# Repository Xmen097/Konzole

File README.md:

# Konzole
Herní konzole s Atmega328 vytvořená v rámci kroužku v DDM Praha 6.

##### Hardware
- TFT display 320x240
- Custom joystick
- 8 tlačítek
- IR vysílač a přijímač
- Otočný potenciometr
- Nabíjecí li-ion baterie s nabíjecím obvodem na micro USB

##### Software
Implementovány byly hry:
 Pong, Tetris, Snake (credits: Vojtěch Černý), pacman, Space shooter

##### Obrázky

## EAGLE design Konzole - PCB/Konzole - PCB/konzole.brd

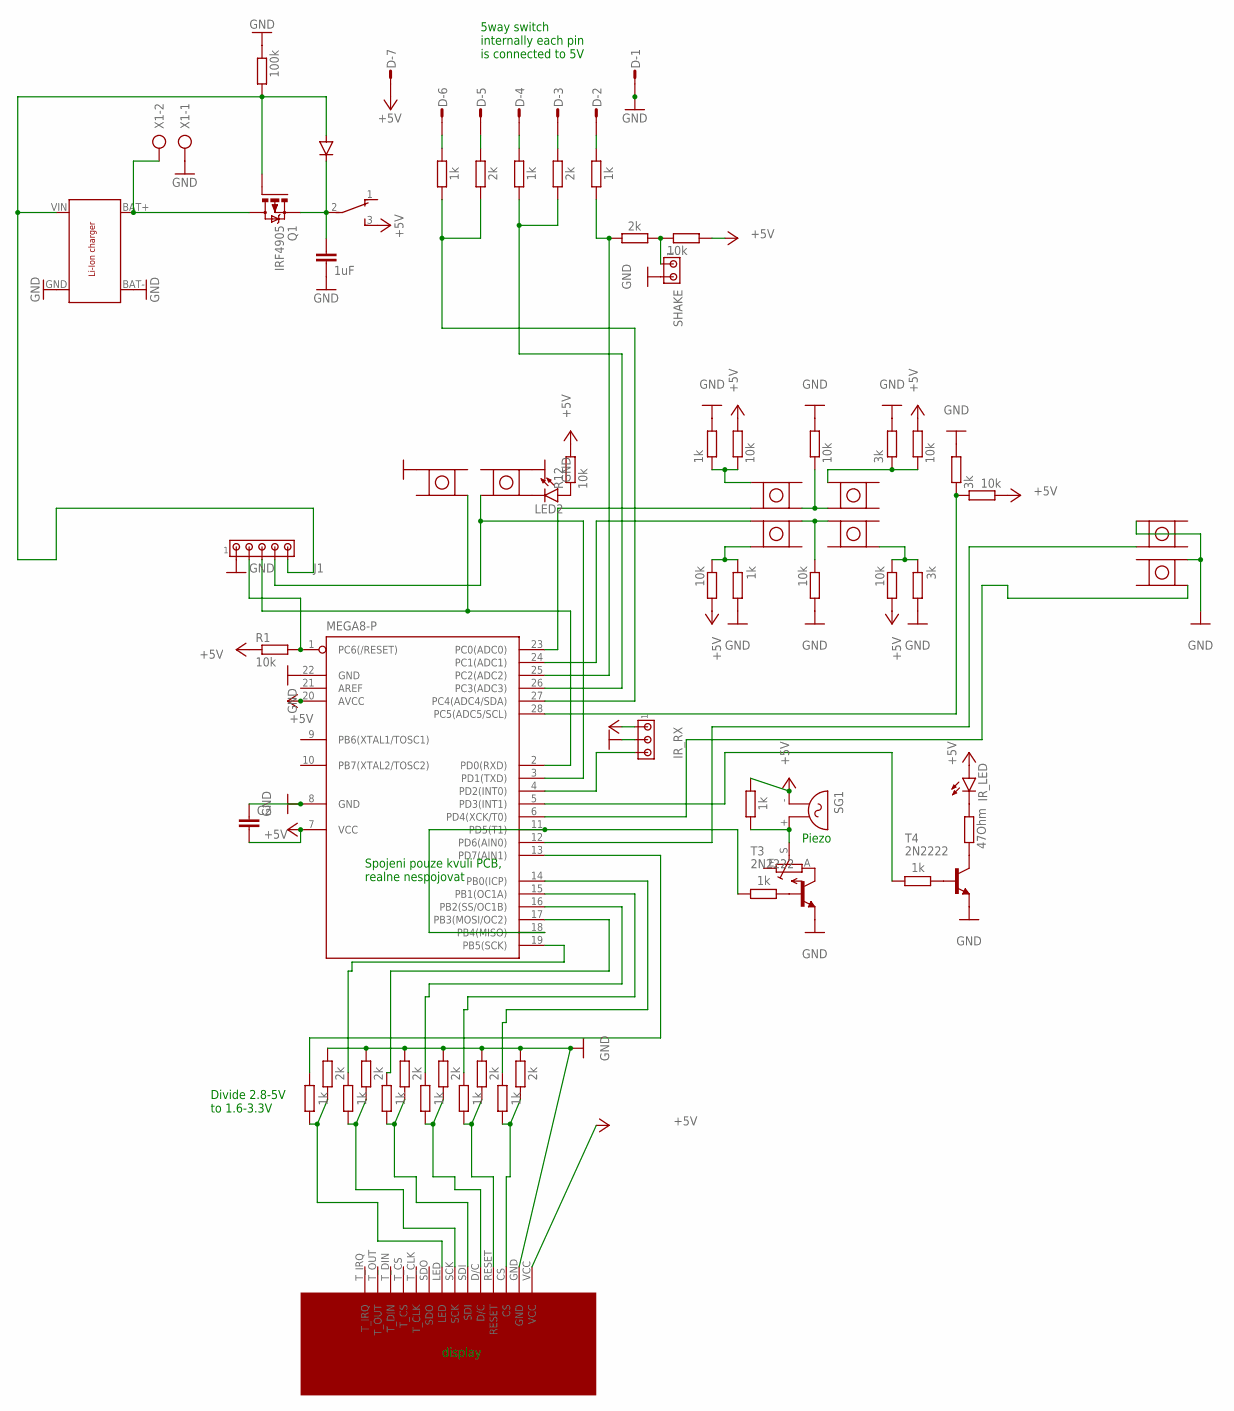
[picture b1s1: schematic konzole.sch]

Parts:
C1: 1uF; C050-025X075
C2: C5/2.5; C5B2.5
D: L07P
D1: 1N4004; DO41-10
IC1: MEGA8-P; DIL28-3
IR_LED: LED5MM
IR_RX: MTA03-100; 10X03MTA
J1: MTA05-100; 10X05MTA
LED2: LED3MM
Q1: IRF4905; TO220BH
R1, R12, R14, R16, R18, R20, R22, R23, R29, R49: 10k; 0207/10
R2, R4, R6, R8, R10, R15, R19, R24, R26, R27, R33, R35, R38, R40: 1k; 0207/10
R3, R5, R7, R9, R11, R25, R36, R39, R41: 2k; 0207/10
R13, R17, R21: 3k; 0207/10
R28: TRIM_EU-CIP20C-6MM; CIP20C-6MM
R34: 47Ohm; 0207/10
R42: 100k; 0207/10
S1: TL36PO; TL3XPO
SG1: F/QMX
SHAKE: MTA02-100; 10X02MTA
T3, T4: 2N2222; TO92-EBC-OVAL
U$1, U$3, U$4, U$5, U$6, U$7, U$8, U$9: TACT
U$2: DISPLAY
U$10: LI_ION_CHARGER
X1: AK500/2

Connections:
+5V: C2.2, D.7, IC1.7 (VCC), IC1.20 (AVCC), IR_LED.A, IR_RX.1, R1.1, R12.2, R14.2, R16.2, R18.2, R20.2, R27.2, R29.1, R49.2, S1.3 (S), SG1.- (1), U$2.VCC
GND: C1.2, C2.1, D.1, IC1.8 (GND), IC1.22 (GND), IR_RX.2, J1.1, R3.2, R5.2, R7.2, R9.2, R11.2, R13.2, R15.2, R17.2, R19.2, R21.2, R22.2, R23.2, R25.2, R42.2, SHAKE.2, T3.E, T4.E, U$2.GND, U$6.P$4 (4), U$7.P$1 (1), U$8.P$1 (1), U$9.P$4 (4), U$10.BAT-, U$10.GND, X1.1
unnamed: IC1.1 (PC6(/RESET)), J1.2, R1.2
unnamed: R2.2, R3.1, U$2.CS
unnamed: R4.2, R5.1, U$2.RESET
unnamed: R6.2, R7.1, U$2.D/C
unnamed: R8.2, R9.1, U$2.SDI
unnamed: R10.2, R11.1, U$2.SCK
unnamed: IC1.17 (PB3(MOSI/OC2)), R8.1
unnamed: IC1.13 (PD7(AIN1)), R24.1
unnamed: IC1.16 (PB2(SS/OC1B)), R6.1
unnamed: IC1.15 (PB1(OC1A)), R4.1
unnamed: R14.1, R15.1, U$1.P$1 (1)
unnamed: R27.1, R28.S, SG1.+ (2)
unnamed: IC1.19 (PB5(SCK)), R10.1
unnamed: R16.1, R17.1, U$5.P$1 (1)
unnamed: R18.1, R19.1, U$3.P$2 (2)
unnamed: R20.1, R21.1, U$4.P$3 (3)
unnamed: R33.2, T4.B
unnamed: LED2.K (C), U$9.P$3 (3)
unnamed: IC1.2 (PD0(RXD)), J1.3, U$8.P$3 (3)
unnamed: IC1.3 (PD1(TXD)), J1.4, U$9.P$2 (2)
unnamed: R23.1, U$3.P$4 (4), U$4.P$1 (1)
unnamed: R22.1, U$1.P$3 (3), U$5.P$2 (2)
unnamed: IC1.23 (PC0(ADC0)), U$1.P$2 (2)
unnamed: R24.2, R25.1, U$2.LED
unnamed: IC1.24 (PC1(ADC1)), U$3.P$1 (1)
unnamed: R34.1, T4.C
unnamed: IC1.11 (PD5(T1)), IC1.18 (PB4(MISO)), R26.1
unnamed: R26.2, T3.B
unnamed: R28.A, T3.C
unnamed: IC1.14 (PB0(ICP)), R2.1
unnamed: IC1.12 (PD6(AIN0)), U$7.P$2 (2)
unnamed: IC1.28 (PC5(ADC5/SCL)), R13.1, R29.2
unnamed: IC1.6 (PD4(XCK/T0)), U$6.P$3 (3)
unnamed: LED2.A, R12.1
unnamed: IC1.4 (PD2(INT0)), IR_RX.3
unnamed: IR_LED.K (C), R34.2
unnamed: IC1.5 (PD3(INT1)), R33.1
unnamed: D.6, R38.2
unnamed: D.5, R36.2
unnamed: D.4, R35.2
unnamed: Q1.D, U$10.BAT+, X1.2
unnamed: D.3, R39.2
unnamed: D.2, R40.2
unnamed: IC1.26 (PC3(ADC3)), R35.1, R39.1
unnamed: R41.1, R49.1, SHAKE.1
unnamed: D1.A, J1.5, Q1.G, R42.1, U$10.VIN
unnamed: C1.1, D1.C, Q1.S, S1.2
unnamed: IC1.25 (PC2(ADC2)), R40.1, R41.2
unnamed: IC1.27 (PC4(ADC4/SDA)), R36.1, R38.1

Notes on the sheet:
Spojeni pouze kvuli PCB, realne nespojovat
display
Divide 2.8-5V to 1.6-3.3V
Piezo
5way switch internally each pin is connected to 5V

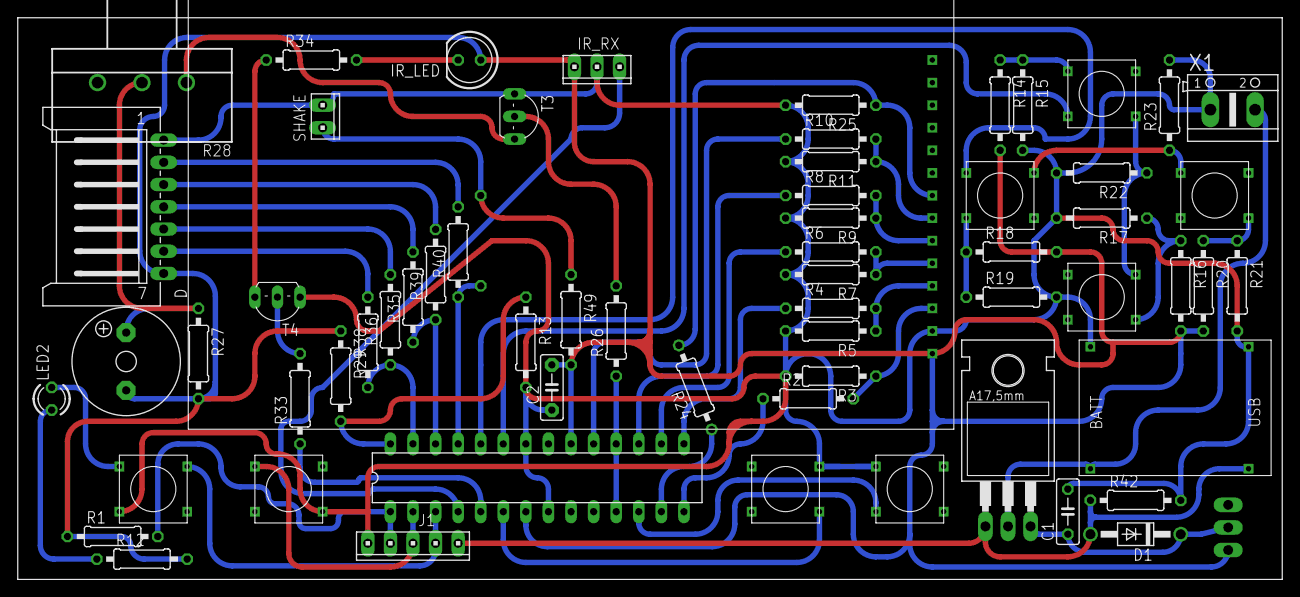
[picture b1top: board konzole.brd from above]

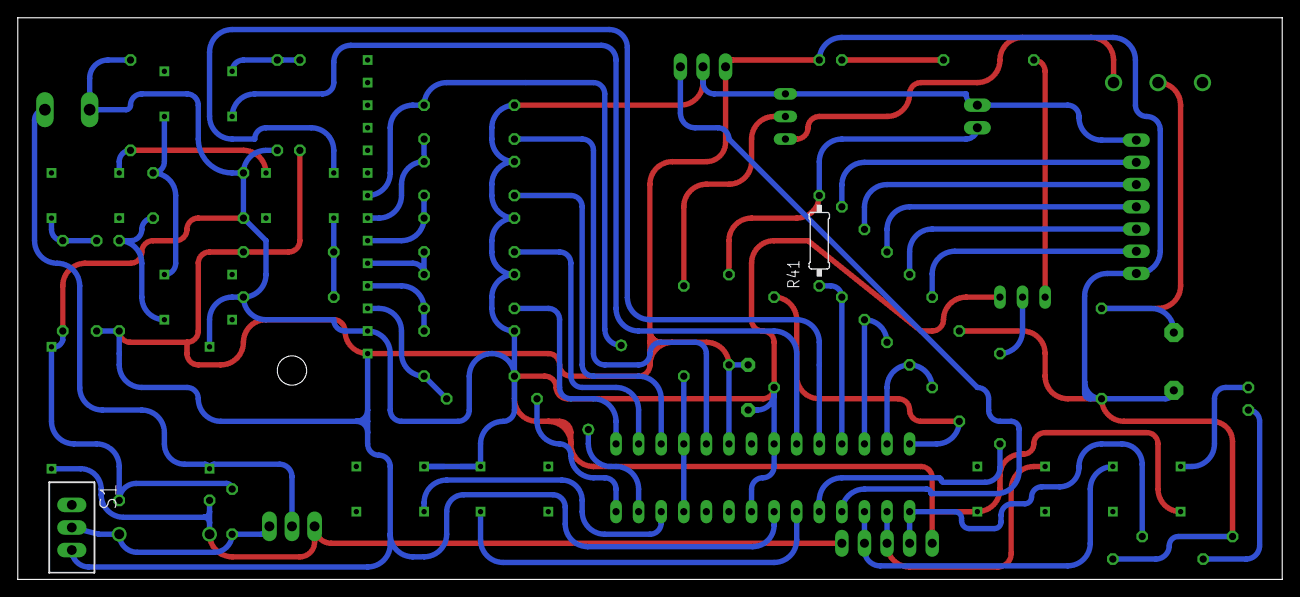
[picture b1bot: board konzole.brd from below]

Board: 2 copper layers, 142.2 x 63.2 mm, 65 parts (2 on the bottom side), 51 nets.

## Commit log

2023-07-13 Added to github
2023-07-13 clean up
2023-07-13 cleanup
